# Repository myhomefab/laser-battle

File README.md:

# Laser-Battle
Indoor and outdoor D.I.Y. Laser Tag Game System

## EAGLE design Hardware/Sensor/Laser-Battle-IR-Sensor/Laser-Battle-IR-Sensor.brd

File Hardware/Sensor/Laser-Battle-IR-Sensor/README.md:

## Laser Battle IR Sensor Circuit Board ##
----------
This is the circuit boards for Laser Battle IR Sensor.  

*.brd (electronic board made with Cadsoft Eagle)  
*.sch (electronic scheme made with Cadsoft Eagle)  

## Laser Battle IR Sensor Cap and Sensor Base ##
----------

Cap (transparent cap) : it's the clear acrylic dome protecting the sensor's pcb.
Base (plastic base) : it's the plastic base to print with a 3D printer that holds pcb and cap.

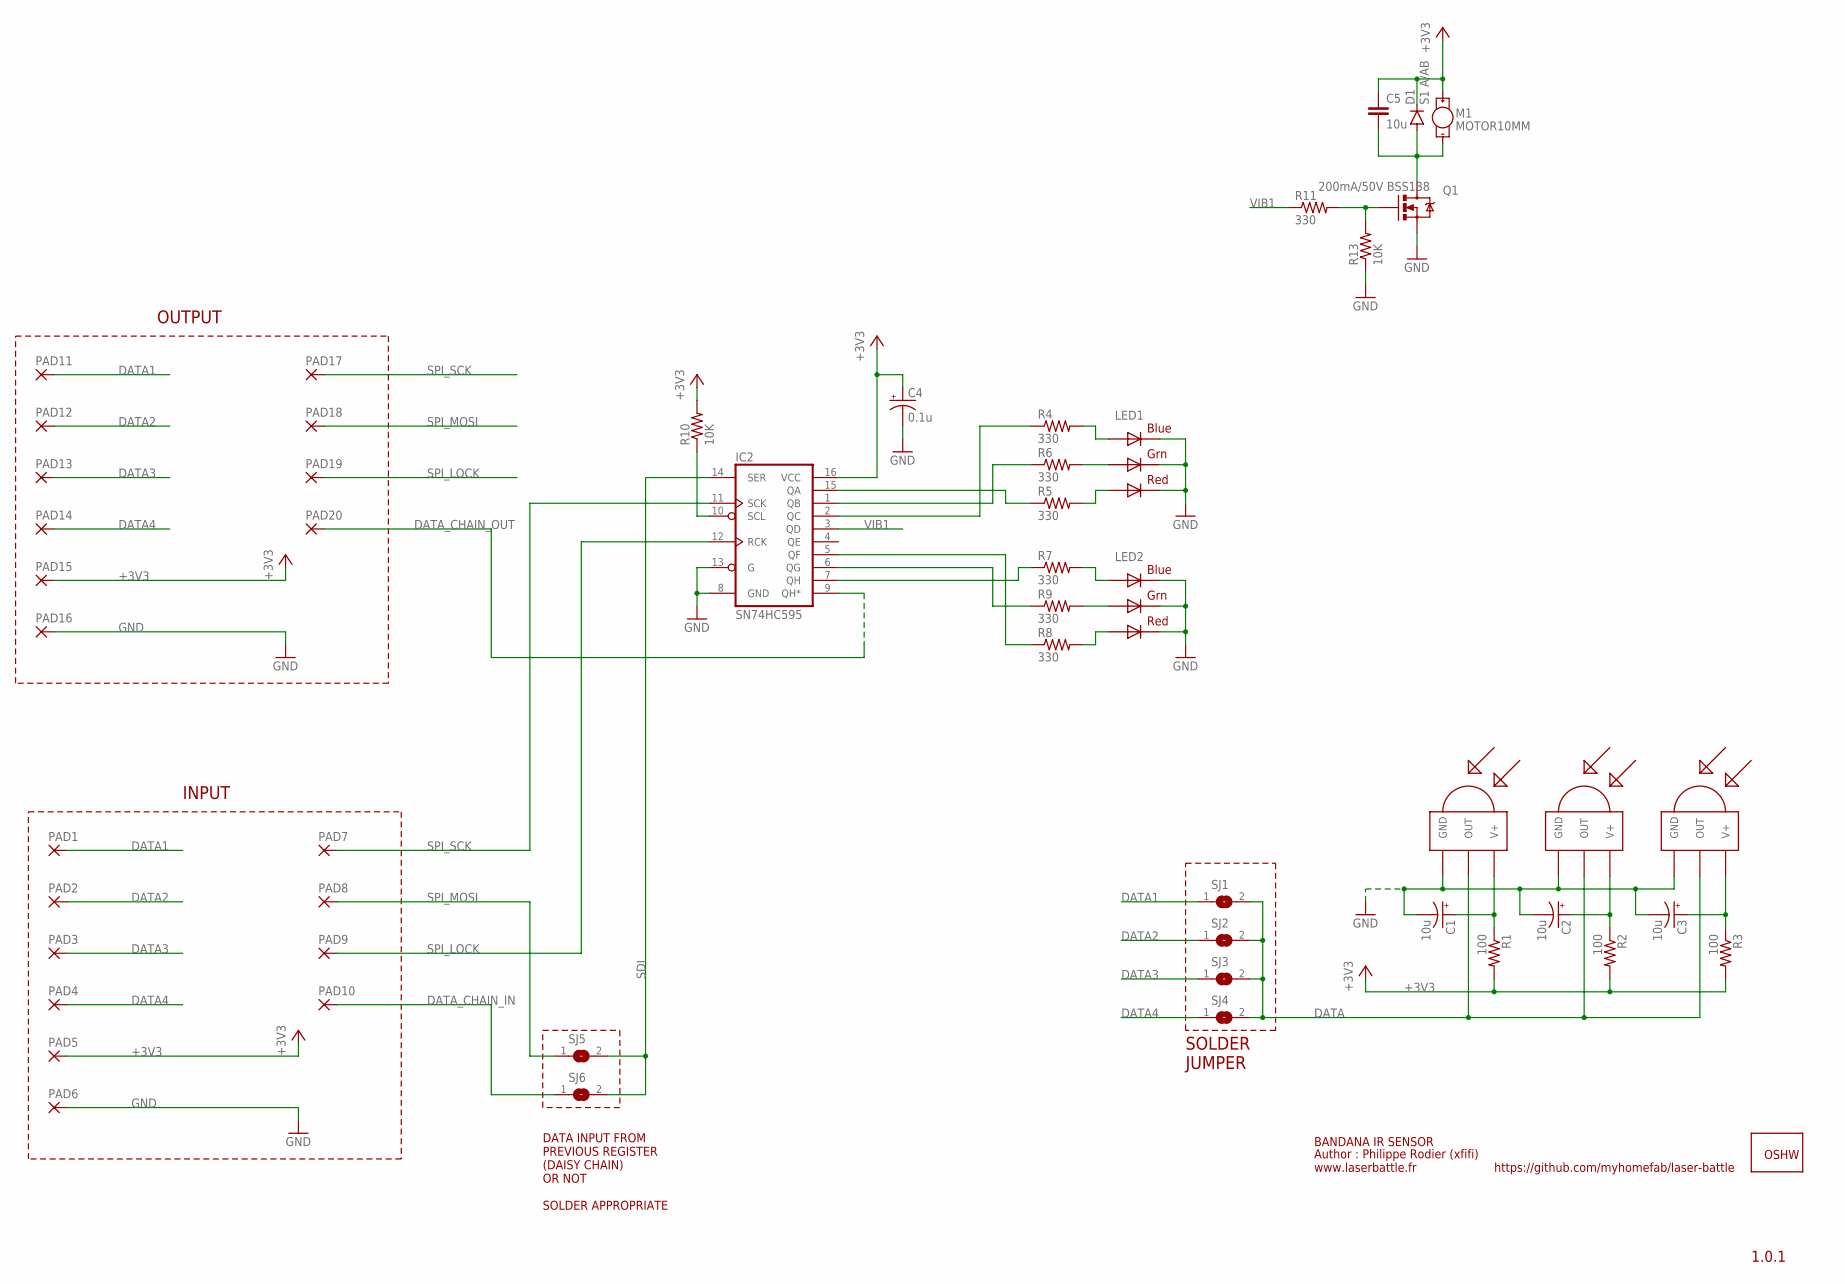
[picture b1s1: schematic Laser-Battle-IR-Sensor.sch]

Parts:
C1, C2, C3: 10u; EIA3216
C4: 0.1u; EIA3216
C5: 10u; 0603-CAP
D1: S1 A/AB; SMA-DIODE
GOLD_ORB_SM1: OSHWLOGO_GOLD_ORB_SM; OSHW2
IC2: SN74HC595; TSSOP16
IR1, IR2, IR3: TSOP4856; TSOP18XX
LED1, LED2: RGBLED5050
M1: MOTOR10MM; VIBE-MOTOR-10MM
PAD1, PAD2, PAD3, PAD4, PAD5, PAD6, PAD7, PAD8, PAD9, PAD10, PAD11, PAD12, PAD13, PAD14, PAD15, PAD16, PAD17, PAD18, PAD19, PAD20: 1,6/0,8
Q1: 200mA/50V BSS138; SOT23-3
R1, R2, R3: 100; 0603-RES
R4, R5, R6, R7, R8, R9, R11: 330; 0603-RES
R10, R13: 10K; 0603-RES
SJ1, SJ2, SJ3, SJ4, SJ5, SJ6: SJ

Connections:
+3V3: C4.A (+), C5.1, D1.C, IC2.16 (VCC), M1.+, PAD5.1, PAD15.1, R1.2, R2.2, R3.2, R10.2
DATA: IR1.OUT, IR2.OUT, IR3.OUT, SJ1.2, SJ2.2, SJ3.2, SJ4.2
DATA1: PAD1.1, PAD11.1, SJ1.1
DATA2: PAD2.1, PAD12.1, SJ2.1
DATA3: PAD3.1, PAD13.1, SJ3.1
DATA4: PAD4.1, PAD14.1, SJ4.1
DATA_CHAIN_IN: PAD10.1, SJ6.1
DATA_CHAIN_OUT: IC2.9 (QH*), PAD20.1
GND: C1.C (-), C2.C (-), C3.C (-), C4.C (-), IC2.8 (GND), IC2.13 (G), IR1.GND, IR2.GND, IR3.GND, LED1.4 (BLUE_C), LED1.5 (RED_C), LED1.6 (GREEN_C), LED2.4 (BLUE_C), LED2.5 (RED_C), LED2.6 (GREEN_C), PAD6.1, PAD16.1, Q1.2 (S), R13.1
unnamed: C3.A (+), IR3.VCC (V+), R3.1
unnamed: C2.A (+), IR2.VCC (V+), R2.1
unnamed: IC2.10 (SCL), R10.1
unnamed: C1.A (+), IR1.VCC (V+), R1.1
unnamed: LED1.3 (BLUE_A), R4.2
unnamed: LED1.1 (GREEN_A), R6.2
unnamed: LED1.2 (RED_A), R5.2
unnamed: LED2.3 (BLUE_A), R7.2
unnamed: LED2.1 (GREEN_A), R9.2
unnamed: LED2.2 (RED_A), R8.2
unnamed: IC2.15 (QA), R5.1
unnamed: IC2.1 (QB), R6.1
unnamed: IC2.2 (QC), R4.1
unnamed: IC2.5 (QF), R8.1
unnamed: IC2.6 (QG), R9.1
unnamed: IC2.7 (QH), R7.1
unnamed: C5.2, D1.A, M1.-, Q1.3 (D)
unnamed: Q1.1 (G), R11.2, R13.2
SDI: IC2.14 (SER), SJ5.2, SJ6.2
SPI_LOCK: IC2.12 (RCK), PAD9.1, PAD19.1
SPI_MOSI: PAD8.1, PAD18.1, SJ5.1
SPI_SCK: IC2.11 (SCK), PAD7.1, PAD17.1
VIB1: IC2.3 (QD), R11.1

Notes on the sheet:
INPUT
OUTPUT
DATA INPUT FROM PREVIOUS REGISTER (DAISY CHAIN) OR NOT SOLDER APPROPRIATE
SOLDER JUMPER
1.0.1
BANDANA IR SENSOR
Author : Philippe Rodier (xfifi) www.laserbattle.fr
https://github.com/myhomefab/laser-battle

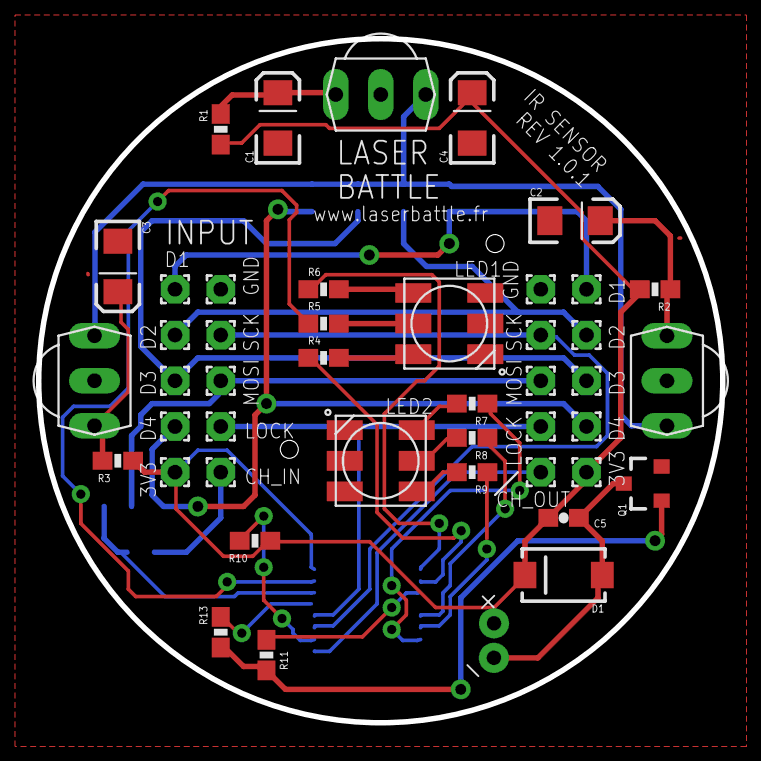
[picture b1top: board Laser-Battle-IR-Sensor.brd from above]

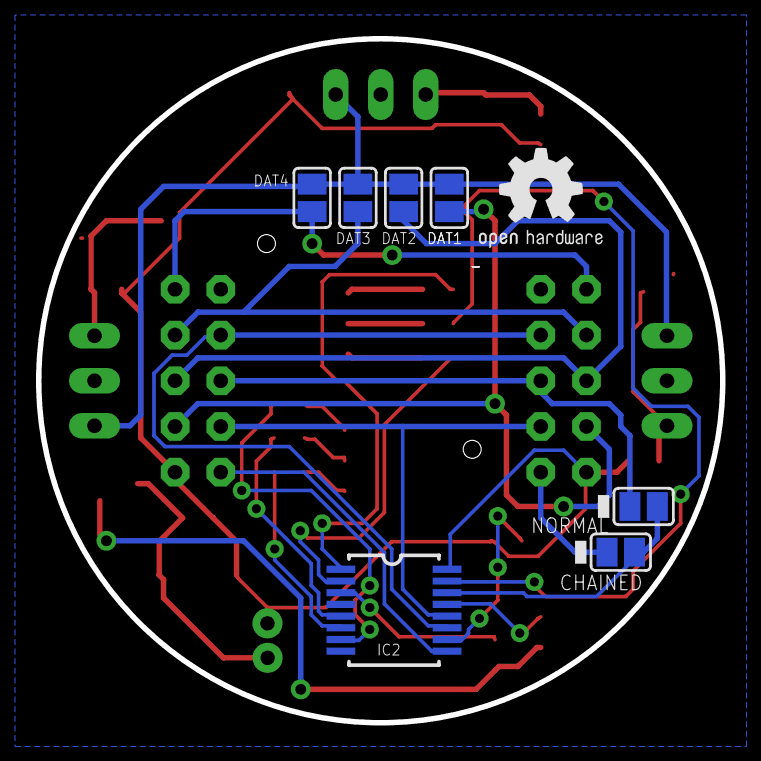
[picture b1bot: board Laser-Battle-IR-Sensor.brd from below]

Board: 2 copper layers, 38.0 x 38.0 mm, 53 parts (8 on the bottom side), 32 nets.

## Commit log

2016-03-28 Added files via upload
2016-04-05 Added files via upload
    3D rendering of PCB
    Rendu 3D de la carte électronique
2016-04-06 Added files via upload
    3D rendering oh the sensor plastic base
2016-04-06 Rename Hardware/Sensor/Laser-Battle-IR-Sensor/Laser-Battle-IR-Sensor.brd to Hardware/Sensor/Laser-Battle-IR-Sensor/Electronic/Laser-Battle-IR-Sensor.brd
2016-04-06 Rename Hardware/Sensor/Laser-Battle-IR-Sensor/sensor-base.md to Hardware/Sensor/Laser-Battle-IR-Sensor/Enclosure/sensor-base.md
2016-04-06 Rename Hardware/Sensor/Laser-Battle-IR-Sensor/sensor-cap.md to Hardware/Sensor/Laser-Battle-IR-Sensor/Enclosure/sensor-cap.md
2018-03-10 Create Laser-Battle-I2C-Sensor

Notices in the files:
parts and their libraries:
SparkFun-Resistors: Licensing: Creative Commons ShareAlike 4.0 International - https://creativecommons.org/licenses/by-sa/4.0
